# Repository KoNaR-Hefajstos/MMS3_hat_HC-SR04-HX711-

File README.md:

# Hat 4x HC-SR04 i Przetwornika Tensometrycznego HX711

## Sekcja 1: Dokumentacja Hat'a

### Krótki opis projektu
Hat obsługuje cztery zewnętrzne ultradźwiękowe czujniki odległości HC-SR04 oraz dwukanałowey, 24-bitowego przetwornika dla belek tensometrycznych HX711.

Sercem modułu jest mikrokontroler **CH32V003**, który odczytuje dane z czujników i udostępnia je do odczytu po I2C

### Zgodność ze standardem ChainBus

* ✅ Używa złącza ChainBus, nie zmienia jego miejsca ani pinoutu.
* ✅ Używa wyłącznie interfejsu I2C do komunikacji zewnętrznej (działa jako Slave, nie inicjuje transmisji jako Master).
* ✅ Spełnia wymagania mechaniczne standardu (wymiary PCB, rozstaw otworów).
* ✅ Pobiera prąd mieszczący się w limitach wyznaczonych dla pojedynczego modułu (CH32V003 może wyzwalać czujniki ultradźwiękowe sekwencyjnie w celu redukcji zakłóceń i szpilek prądowych).
* ✅ Obsługuje napięcie wejściowe BRD_VIN do wartości 48V.

### Komunikacja i adresowanie

#### Adresacja I2C
Komunikacja z modułem nadrzędnym odbywa się przez magistralę I2C. Adres mikrokontrolera CH32V003 jest definiowany programowo.

| Układ (IC)   | Funkcja                               |     Adres I2C (7-bit)     |
| :----------- | :------------------------------------ | :-----------------------: |
| **CH32V003** | Mikrokontroler (konwerter protokołów) | *Konfigurowalny w sofcie* |
| **M24C64-W** | Pamięć EEPROM (identyfikacja modułu)  |     `1010000b` (0x50)     |

### Pinout mikrokontrolera CH32V003

Rozprowadzenie sygnałów sterujących na piny mikrokontrolera przedstawia poniższa tabela:

| Pin MCU | Nazwa sygnału | Kierunek | Opis funkcjonalny                                              |
| :------ | :------------ | :------: | :------------------------------------------------------------- |
| **PC0** | `ECHO #1`     | Wejście  | Sygnał Echo z czujnika ultradźwiękowego nr 1                   |
| **PC1** | `SDA`         | Wej/Wyj  | Linia danych magistrali I2C (ChainBus)                         |
| **PC2** | `SCL`         | Wejście  | Linia zegarowa magistrali I2C (ChainBus)                       |
| **PC3** | `TRIG #1`     | Wyjście  | Sygnał wyzwalający (Trigger) dla czujnika nr 1                 |
| **PC4** | `ECHO #2`     | Wejście  | Sygnał Echo z czujnika ultradźwiękowego nr 2                   |
| **PC5** | `TRIG #2`     | Wyjście  | Sygnał wyzwalający (Trigger) dla czujnika nr 2                 |
| **PC6** | `ECHO #3`     | Wejście  | Sygnał Echo z czujnika ultradźwiękowego nr 3                   |
| **PC7** | `TRIG #3`     | Wyjście  | Sygnał wyzwalający (Trigger) dla czujnika nr 3                 |
| **PD0** | `ECHO #4`     | Wejście  | Sygnał Echo z czujnika ultradźwiękowego nr 4                   |
| **PD2** | `TRIG #4`     | Wyjście  | Sygnał wyzwalający (Trigger) dla czujnika nr 4                 |
| **PD3** | `RATE_HX`     | Wyjście  | Wybór prędkości próbkowania HX711 (`0` = 10 SPS, `1` = 80 SPS) |
| **PD4** | `PD_SCK_HX`   | Wyjście  | Zegar transmisji oraz wyłączenie zasilania (Power Down) HX711  |
| **PD5** | `DEBUG_TX`    | Wyjście  | Wyjście do debugowania (USART TX)                              |
| **PD6** | `DOUT_HX`     | Wejście  | Wyjście danych szeregowych z przetwornika HX711                |

Dodatkowo na PD6 jest podłączona dioda, można jej użyć do debugowania
---

### Pinout złączy zewnętrznych

#### Złącza czujników ultradźwiękowych
Moduł posiada cztery  złącza w do podłączenia czujników odległości HC-SR04.

| Pin złącza | Nazwa sygnału | Opis                                          |
| :--------: | :------------ | :-------------------------------------------- |
|   **1**    | `5V`          | Zasilanie czujnika (5V z magistrali ChainBus) |
|   **2**    | `TRIG`        | Sygnał wyzwalający                            |
|   **3**    | `ECHO`        | Sygnał powrotny                               |
|   **4**    | `GND`         | Masa zasilania                                |

#### Złącze belki tensometrycznej (J5)
Złącze przeznaczone do podłączenia czujnika siły / wagi (belki tensometrycznej w układzie mostka Wheatstone'a). Sygnały wejściowe są dopasowane do specyfikacji Kanału B układu HX711.

| Pin złącza | Nazwa sygnału | Opis                                              |
| :--------: | :------------ | :------------------------------------------------ |
|   **1**    | `EX+` (E+)    | Dodatnie napięcie zasilania mostka (Excitation +) |
|   **2**    | `INB+`        | Dodatni sygnał wyjściowy z mostka (Input B+)      |
|   **3**    | `INB-`        | Ujemny sygnał wyjściowy z mostka (Input B-)       |
|   **4**    | `GND` (E-)    | Masa zasilania mostka (Excitation -)              |

#### Złącze programowania mikrokontrolera (J7)
Złącze debugowania i programowania struktury CH32V003 przy użyciu WCH Link-E.

| Pin złącza | Nazwa sygnału | Opis                                                      |
| :--------: | :------------ | :-------------------------------------------------------- |
|   **1**    | `SWIO`        | Linia danych SWD (podłączona do pinu PD1 mikrokontrolera) |
|   **2**    | `GND`         | Masa odniesienia                                          |
|   **3**    | `3V3`         | Zasilanie układu logiki (3.3V)                            |

---
### Szczegółowy opis działania układu

#### Sekcja ultradźwiękowa (HC-SR04)
Mikrokontroler CH32V003 cyklicznie generuje impuls wyzwalający piny `TRIG x`. Następnie mierzy czas trwania stanu wysokiego na powiązanym pinie `ECHO x`. Pomiar ten jest przeliczany na odległość zapisywany w rejestrach wewnętrznych MCU, gotowych do odczytu przez magistralę I2C.

#### Sekcja wagowa (HX711)
Układ HX711 przetwarza mikrowoltowe różnice napięć z mostka tensometrycznego na postać cyfrową.
* **Proces odczytu:** MCU monitoruje stan linii `DOUT_HX` (PD6). Gdy linia przejdzie w stan niski, oznacza to gotowość danych. Mikrokontroler taktuje linię `PD_SCK_HX` (PD4), odczytując kolejno 24 bity danych, a następnie generuje dodatkowe impulsy w celu konfiguracji następnego pomiaru (np. 26 impulsów, aby utrzymać odczyt z Kanału B ze wzmocnieniem 32).

#### Charakterystyka i parametry przetwornika HX711

Układ HX711 jest dedykowanym, 24-bitowym przetwornikiem ADC ze zintegrowanym niskoszumnym przedwzmacniaczem (PGA). Posiada on dwa różnicowe kanały wejściowe, które różnią się zakresem napięć oraz czułością:

#### Różnice między Kanałem A i Kanałem B

1. **Wzmocnienie i zakresy wejściowe (przy zasilaniu $V_{DD} = 5\text{V}$):**
   * **Kanał A:** Posiada programowalny stopień wzmocnienia równy **128** lub **64**.
     * Dla wzmocnienia **128**: zakres napięcia wejściowego wynosi **$\pm 20\text{ mV}$** (pełna skala). Jest to najbardziej czuły zakres, zalecany dla większości typowych belek tensometrycznych.
     * Dla wzmocnienia **64**: zakres napięcia wejściowego wynosi **$\pm 40\text{ mV}$**.
   * **Kanał B:** Posiada stałe, fabrycznie zdefiniowane wzmocnienie **32**.
     * Zakres napięcia wejściowego wynosi **$\pm 80\text{ mV}$**. Kanał ten, dzięki szerszemu zakresowi i mniejszej czułości, doskonale nadaje się do obsługi czujników o wyższym poziomie sygnału wyjściowego lub pomiarów pomocniczych.

2. **Wybór aktywnego kanału:**
   Multipleksacja kanałów wejściowych odbywa się programowo poprzez podanie odpowiedniej liczby impulsów zegarowych na pin `PD_SCK` po odczytaniu danych (wejście `DOUT` w stanie niskim):
   * **25 impulsów zegarowych:** następny pomiar na Kanale A ze wzmocnieniem 128,
   * **26 impulsów zegarowych:** następny pomiar na Kanale B ze wzmocnieniem 32,
   * **27 impulsów zegarowych:** następny pomiar na Kanale A ze wzmocnieniem 64.

3. **Częstotliwość próbkowania (SPS):**
   Prędkość konwersji jest ustawiana sprzętowo poprzez stan pinu `RATE_HX` (PD3):
   * Stan niski (`0`): **10 SPS** (próbek na sekundę). Zapewnia najniższy poziom szumów i najwyższą stabilność pomiarów wagowych (zalecane).
   * Stan wysoki (`1`): **80 SPS**. Zwiększa dynamikę pomiarów kosztem nieznacznego wzrostu szumu przetwornika.

---

---

### Gotowe arkusze hierarchiczne
W projekcie zaprojektowano i użyto następujących arkuszy hierarchicznych:
* **CH32v003** – Arkusz mikrokontrolera
* **Ultrasonic_HC-SR04** – Arkusz z podłączeniem HC-SR04 oraz dzielnikami napięcie 5V -> 3V3.
* **HX711_LoadCell** – Układ przetwornika HX711 ze wszytkimi elementami pasywnymi i złaczem

---

## Sekcja 2: Specyfikacja standardu ChainBus

### Architektura i łączenie modułów
Standard ChainBus umożliwia modułowe łączenie hatów. Na jednym MMS3 można zamontować pionowo **do 8 hat'ów**. Połączenie realizowane jest poprzez wpięcie złącza męskiego kolejnego hat'a w złącze żeńskie poprzedniego.

### Komunikacja i sterowanie
Magistrala ChainBus jest w pełni cyfrowa. Płyta główna nie steruje bezpośrednio sygnałami ogólnego przeznaczenia (GPIO) na poszczególnych hat'ach. Wszelkie operacje (np. odczyt czujników, sterowanie) muszą być realizowane przez dedykowane układy scalone komunikujące się przez interfejsy systemowe.

Wybór aktywnego modułu realizowany jest przez układ przełącznika magistrali (bus switch) na płycie głównej. Dzięki temu linie I2C, SPI i UART są niezależne dla każdego hat'a (brak konfliktów adresów I2C między różnymi hatami).
* **Identyfikacja:** Każdy moduł powinien posiadać pamięć EEPROM na magistrali I2C w celu identyfikacji płyty przez system - układ M24C64-W skonfigurowany na adres `1010000` przy liniach adresowych A0, A1, A2 zwartych do masy.

### Zasilanie
Złącze ChainBus dostarcza następujące linie zasilania:

| Magistrala zasilania | Napięcie znamionowe | Maksymalny prąd (łączny dla 8 hatów) | Szacowany prąd na jeden hat |
| :------------------- | :-----------------: | :----------------------------------: | :-------------------------: |
| **5V**               |        5.0 V        |                1.0 A                 |           125 mA            |
| **12V stby**         |       12.0 V        |                0.5 A                 |            65 mA            |
| **BRD_VIN**          |   12.0 V – 48.0 V   |                1.5 A                 |           185 mA            |

*   Komponenty podłączone do linii `BRD_VIN` muszą być przystosowane do pracy z napięciem od 12V do **48 V**.

---

## Sekcja 3: Licencje

### Licencje projektu

*   **PCB:** CERN-OHL-P
*   **Software:** MIT License

[Template](https://github.com/KoNaR-Hefajstos/MMS3_hat_templates/) jest na licencji CC0 1.0 Universal. **Reszta projektu nie jest na tej licencji**

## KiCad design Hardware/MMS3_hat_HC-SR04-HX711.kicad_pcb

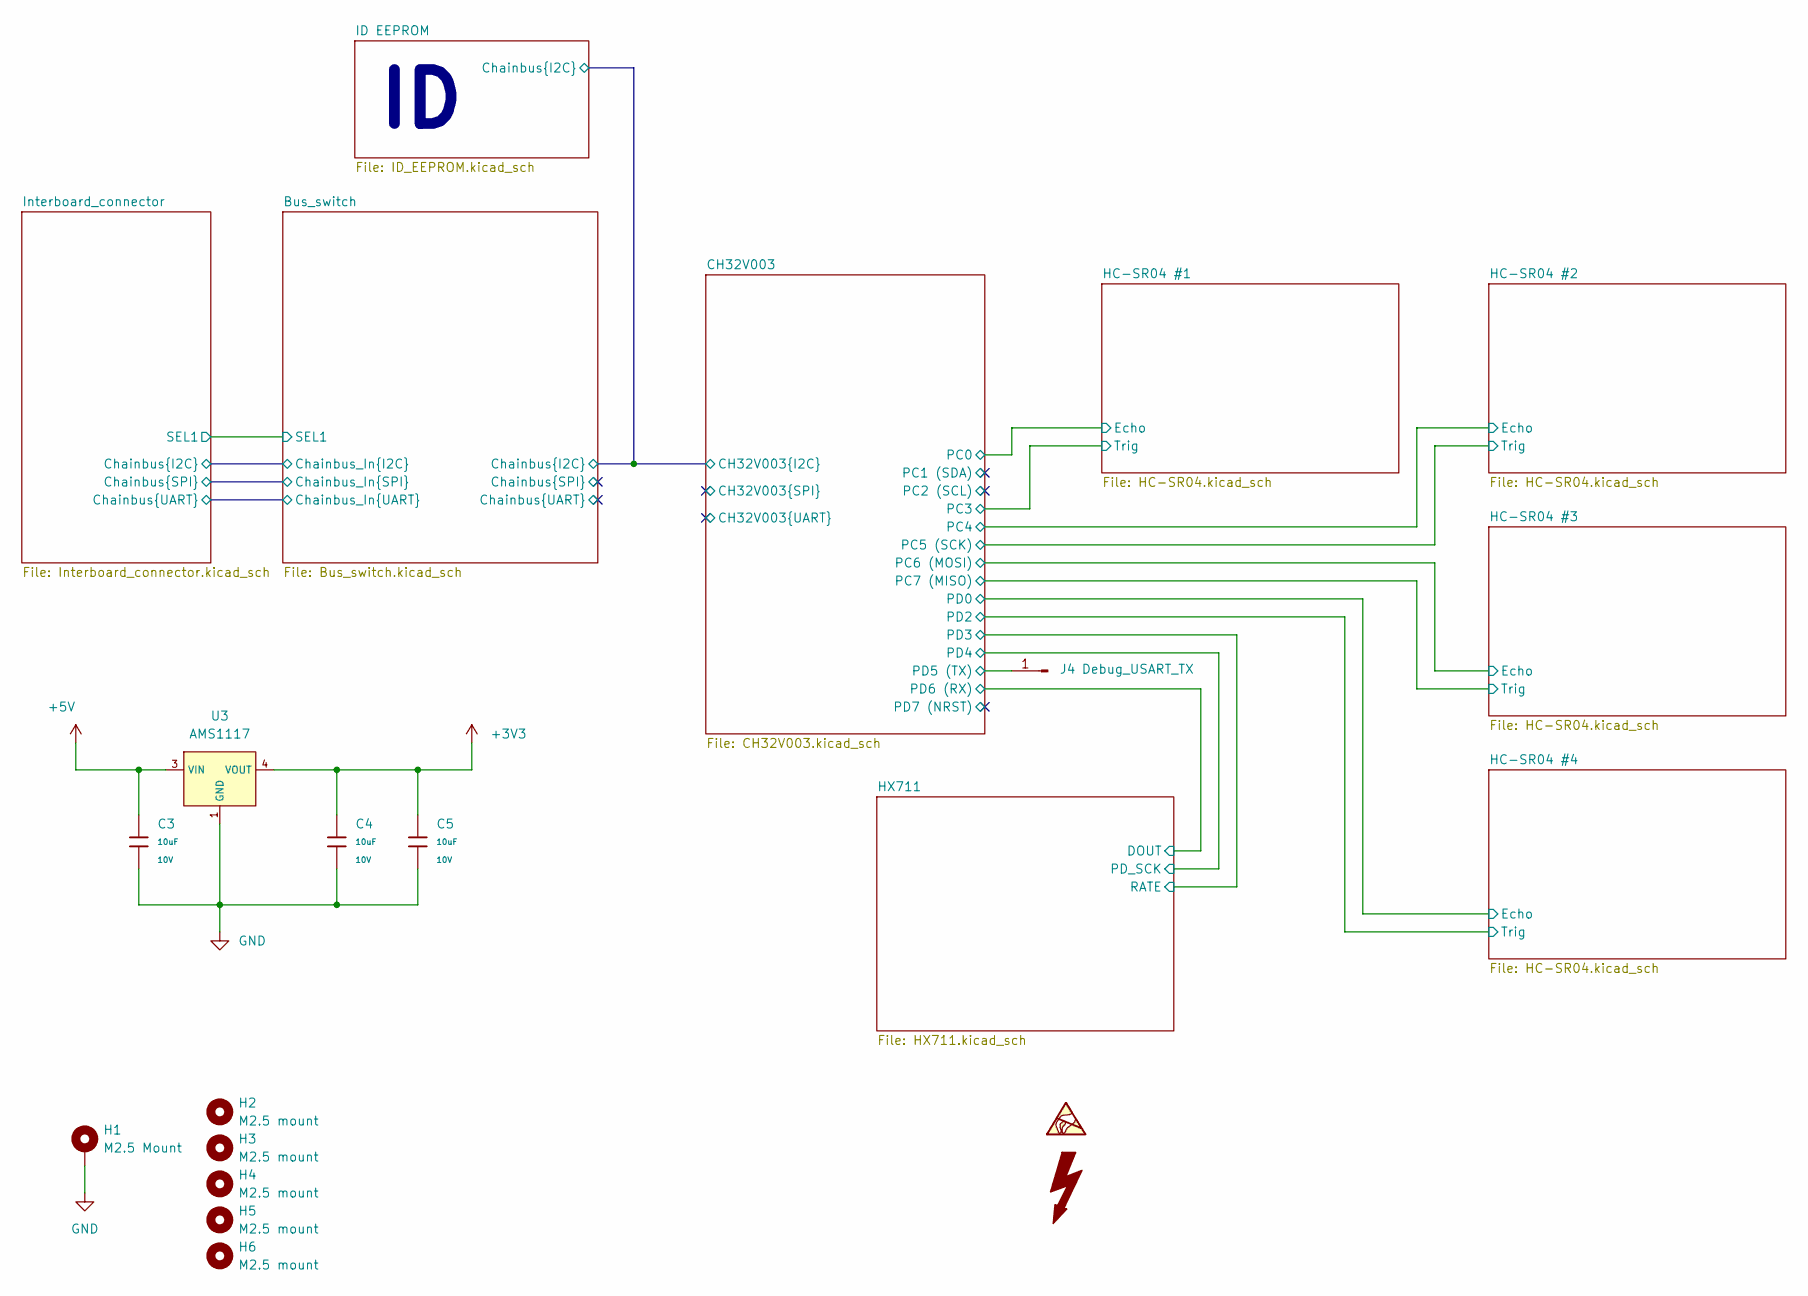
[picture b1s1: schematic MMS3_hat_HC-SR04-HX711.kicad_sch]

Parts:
C3, C4, C5: 10uF; C_0603; Voltage Rated 10V; Tolerance ±10%; Part CL10A106KP8NNNC; LCSC C19702
H1: M2.5 Mount; MountingHole_2.7mm_M2.5_DIN965_Pad_TopOnly
H2, H3, H4, H5, H6: M2.5 mount; MountingHole_2.7mm_M2.5
J4: Debug_USART_TX; PinSocket_1x01_P2.54mm_Vertical
U3: AMS1117; SOT-223-3_L6.5-W3.4-P2.30-LS7.0-BR; Output Voltage 3.3V; Dropout Voltage 1.3V@(800mA); Part AMS1117-3.3; LCSC C6186

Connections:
+3V3: C4.1, C5.1, U3.2 (VOUT), U3.4 (VOUT); also elsewhere on the board
+5V: C3.1, U3.3 (VIN); also elsewhere on the board
/CH32V003/CH32V003.TX: J4.1 (Pin_1_1); also elsewhere on the board
GND: C3.2, C4.2, C5.2, H1.1 (1_1), U3.1 (GND); also elsewhere on the board

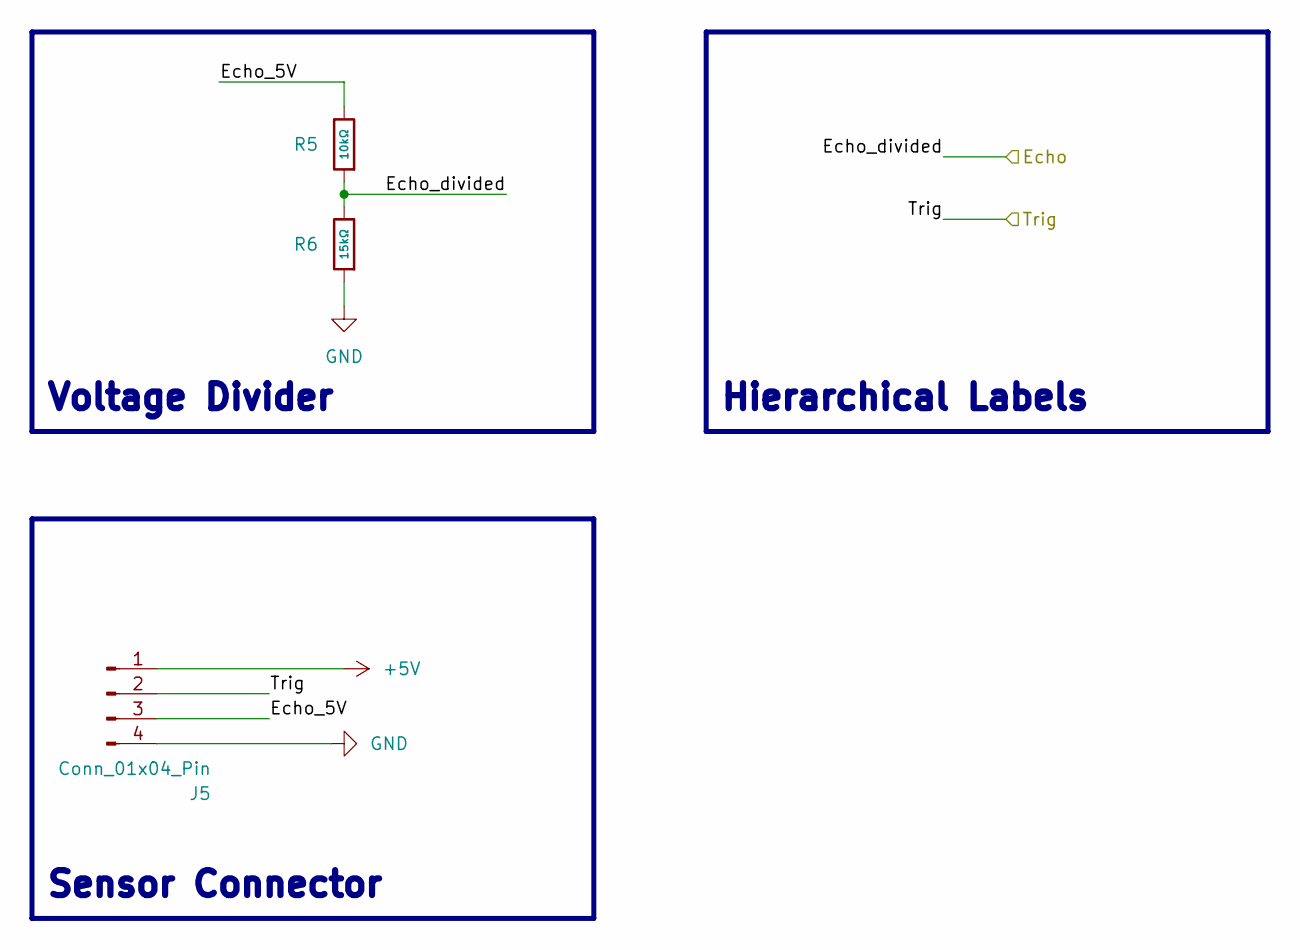
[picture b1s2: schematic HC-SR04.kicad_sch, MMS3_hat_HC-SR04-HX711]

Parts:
J5: Conn_01x04_Pin; JST_XH_S4B-XH-A_1x04_P2.50mm_Horizontal
R5: 10kΩ; R_0402; Overload Voltage (Max) 50V; Tolerance ±1%; Part 0402WGF1002TCE; LCSC C25744
R6: 15kΩ; R_0402; Overload Voltage (Max) 50V; Tolerance ±1%; Part 0402WGF1502TCE; LCSC C25756

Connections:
+5V: J5.1; also elsewhere on the board
/CH32V003/PC0: R5.1, R6.2; also elsewhere on the board
/CH32V003/PC3: J5.2; also elsewhere on the board
/HC-SR04 #1/Echo_5V: J5.3, R5.2
GND: J5.4, R6.1; also elsewhere on the board

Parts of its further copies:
J6, J10, J11: Conn_01x04_Pin; JST_XH_S4B-XH-A_1x04_P2.50mm_Horizontal
R7, R19, R21: 10kΩ; R_0402; Overload Voltage (Max) 50V; Tolerance ±1%; Part 0402WGF1002TCE; LCSC C25744
R8, R20, R22: 15kΩ; R_0402; Overload Voltage (Max) 50V; Tolerance ±1%; Part 0402WGF1502TCE; LCSC C25756

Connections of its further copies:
+5V: J6.1, J10.1, J11.1; also elsewhere on the board
/CH32V003/CH32V003.MISO: J11.2; also elsewhere on the board
/CH32V003/CH32V003.MOSI: R21.1, R22.2; also elsewhere on the board
/CH32V003/CH32V003.SCK: J6.2; also elsewhere on the board
/CH32V003/PC4: R7.1, R8.2; also elsewhere on the board
/CH32V003/PD0: R19.1, R20.2; also elsewhere on the board
/CH32V003/PD2: J10.2; also elsewhere on the board
/HC-SR04 #2/Echo_5V: J6.3, R7.2
/HC-SR04 #3/Echo_5V: J11.3, R21.2
/HC-SR04 #4/Echo_5V: J10.3, R19.2
GND: J6.4, J10.4, J11.4, R8.1, R20.1, R22.1; also elsewhere on the board

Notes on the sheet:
Voltage Divider
Sensor Connector
Hierarchical Labels

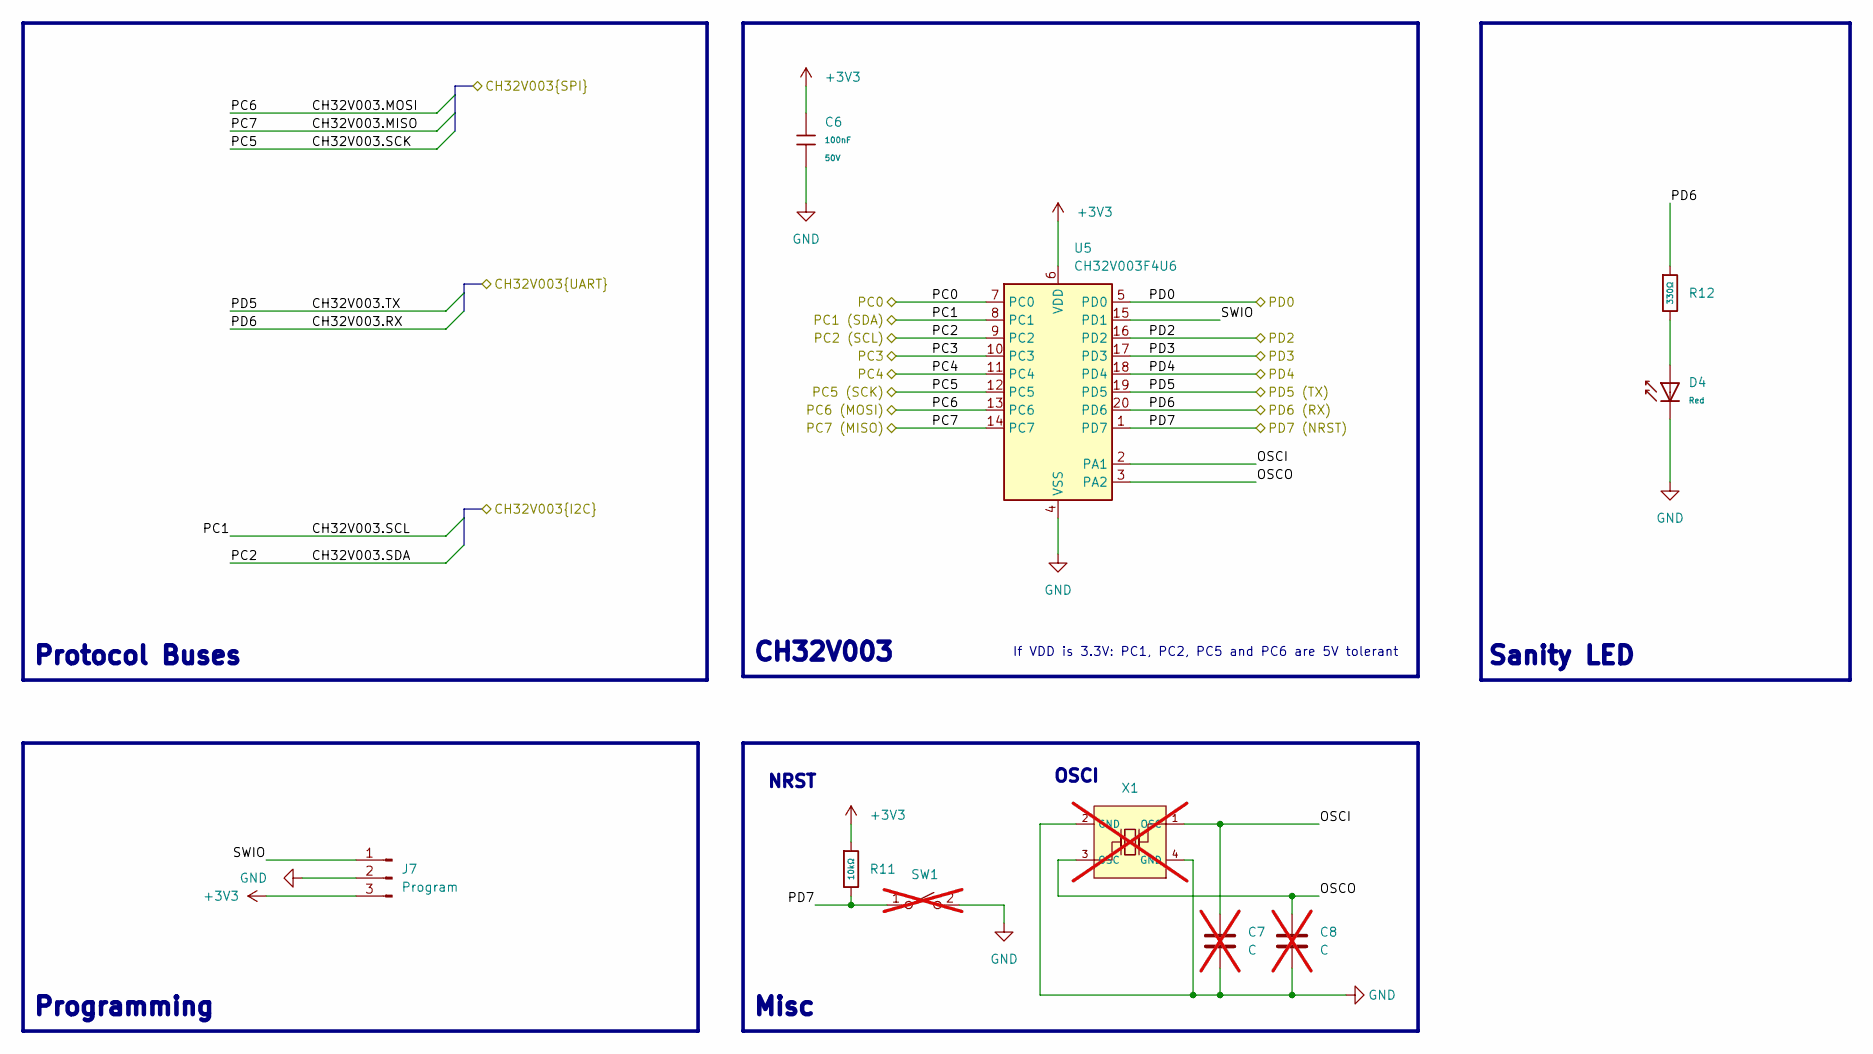
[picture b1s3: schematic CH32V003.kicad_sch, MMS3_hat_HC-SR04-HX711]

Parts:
C6: 100nF; C_0603; Voltage Rated 50V; Tolerance ±10%; Part CC0603KRX7R9BB104; LCSC C14663
C7, C8: C; not fitted
D4: Red; D_0603; Part KT-0603R; LCSC C2286
J7: Program; JST_XH_B3B-XH-A_1x03_P2.50mm_Vertical
R11: 10kΩ; R_0402; Overload Voltage (Max) 50V; Tolerance ±1%; Part 0402WGF1002TCE; LCSC C25744
R12: 330Ω; R_0402; Overload Voltage (Max) 50V; Tolerance ±1%; Part 0402WGF3300TCE; LCSC C25104
SW1: SW_SPST; not fitted
U5: CH32V003F4U6; QFN-20-1EP_3x3mm_P0.4mm_EP1.65x1.65mm; LCSC C5299908
X1: X322525MOB4SI; OSC-SMD_4P-L3.2-W2.5-BL; Frequency Tolerance ±10ppm; Part X322525MOB4SI; LCSC C9006; not fitted

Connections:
+3V3: C6.1, J7.3, R11.1, U5.6 (VDD); also elsewhere on the board
/Bus_switch/Chainbus.SCL: U5.8 (PC1); also elsewhere on the board
/Bus_switch/Chainbus.SDA: U5.9 (PC2); also elsewhere on the board
/CH32V003/CH32V003.MISO: U5.14 (PC7); also elsewhere on the board
/CH32V003/CH32V003.MOSI: U5.13 (PC6); also elsewhere on the board
/CH32V003/CH32V003.RX: R12.1, U5.20 (PD6); also elsewhere on the board
/CH32V003/CH32V003.SCK: U5.12 (PC5); also elsewhere on the board
/CH32V003/CH32V003.TX: U5.19 (PD5); also elsewhere on the board
/CH32V003/OSCI: C7.1, U5.2 (PA1), X1.1 (OSC)
/CH32V003/OSCO: C8.1, U5.3 (PA2), X1.3 (OSC)
/CH32V003/PC0: U5.7 (PC0); also elsewhere on the board
/CH32V003/PC3: U5.10 (PC3); also elsewhere on the board
/CH32V003/PC4: U5.11 (PC4); also elsewhere on the board
/CH32V003/PD0: U5.5 (PD0); also elsewhere on the board
/CH32V003/PD2: U5.16 (PD2); also elsewhere on the board
/CH32V003/PD3: U5.17 (PD3); also elsewhere on the board
/CH32V003/PD4: U5.18 (PD4); also elsewhere on the board
/CH32V003/PD7: R11.2, SW1.1 (A), U5.1 (PD7)
/CH32V003/SWIO: J7.1, U5.15 (PD1)
GND: C6.2, C7.2, C8.2, D4.1, J7.2, SW1.2 (B), U5.4 (VSS), U5.21 (VSS), X1.2 (GND), X1.4 (GND); also elsewhere on the board
unnamed: D4.2, R12.2

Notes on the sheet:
NRST
Sanity LED
If VDD is 3.3V: PC1, PC2, PC5 and PC6 are 5V tolerant
CH32V003
OSCI
Protocol Buses
Misc
Programming

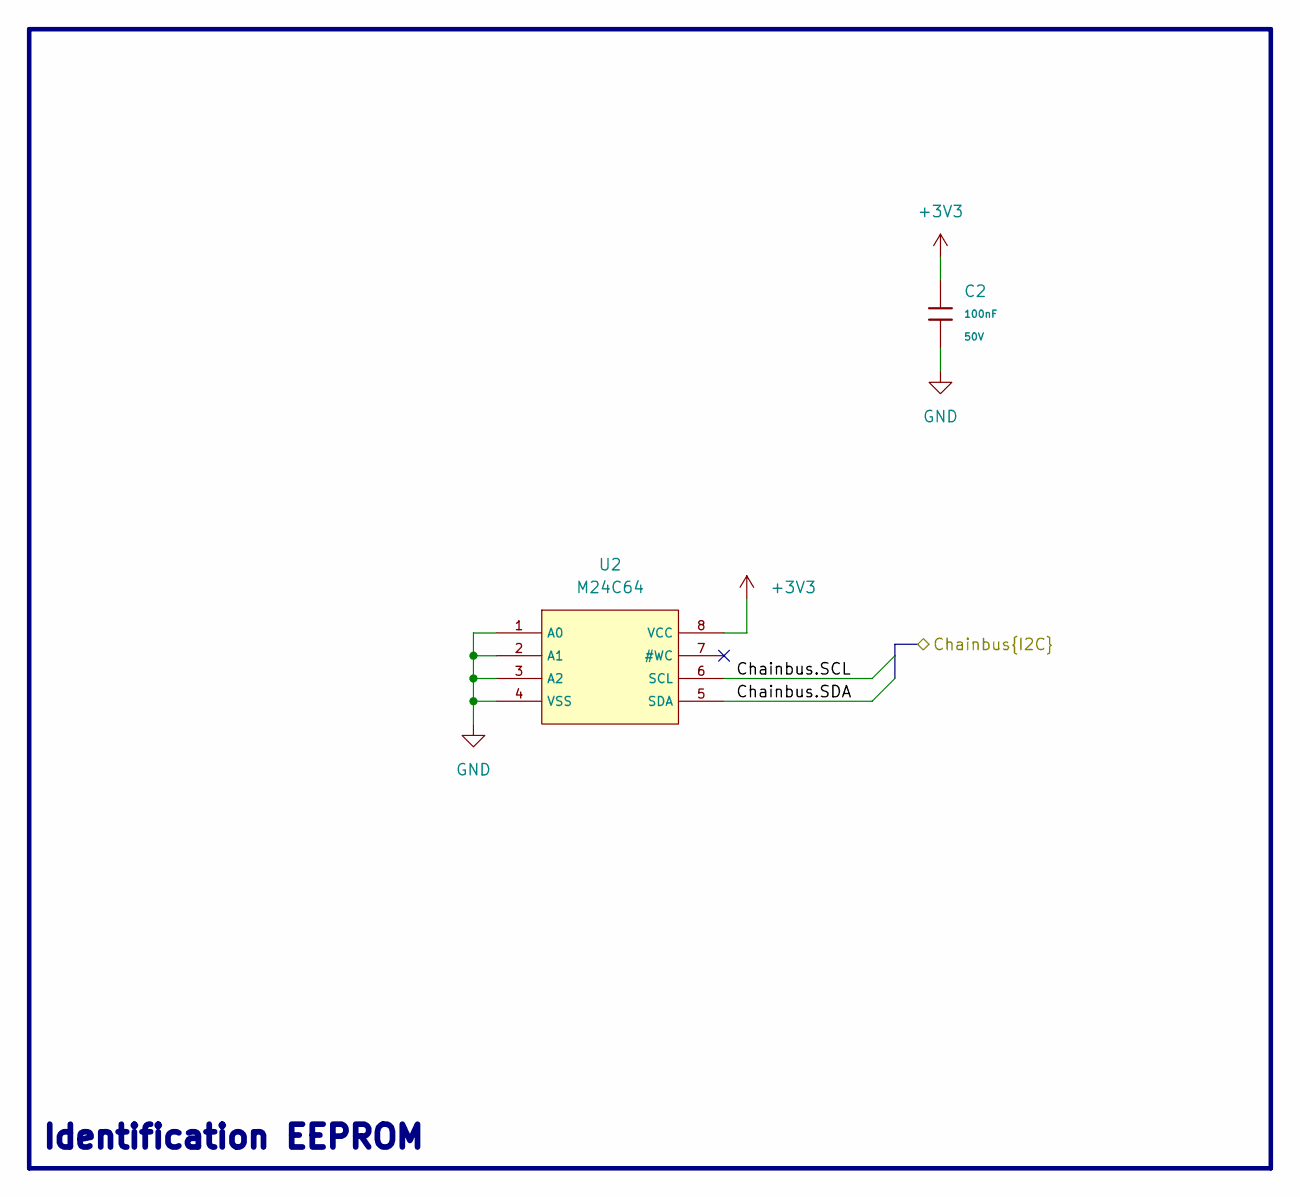
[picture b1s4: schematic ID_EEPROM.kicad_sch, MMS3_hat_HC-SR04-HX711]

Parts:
C2: 100nF; C_0603; Voltage Rated 50V; Tolerance ±10%; Part CC0603KRX7R9BB104; LCSC C14663
U2: M24C64; SOIC-8_L5.0-W4.0-P1.27-LS6.0-BL; Supply Voltage 1.8V~5.5V; Part M24C64-RMN6TP; LCSC C79988

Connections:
+3V3: C2.1, U2.8 (VCC); also elsewhere on the board
/Bus_switch/Chainbus.SCL: U2.6 (SCL); also elsewhere on the board
/Bus_switch/Chainbus.SDA: U2.5 (SDA); also elsewhere on the board
GND: C2.2, U2.1 (A0), U2.2 (A1), U2.3 (A2), U2.4 (VSS); also elsewhere on the board

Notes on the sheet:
Identification EEPROM

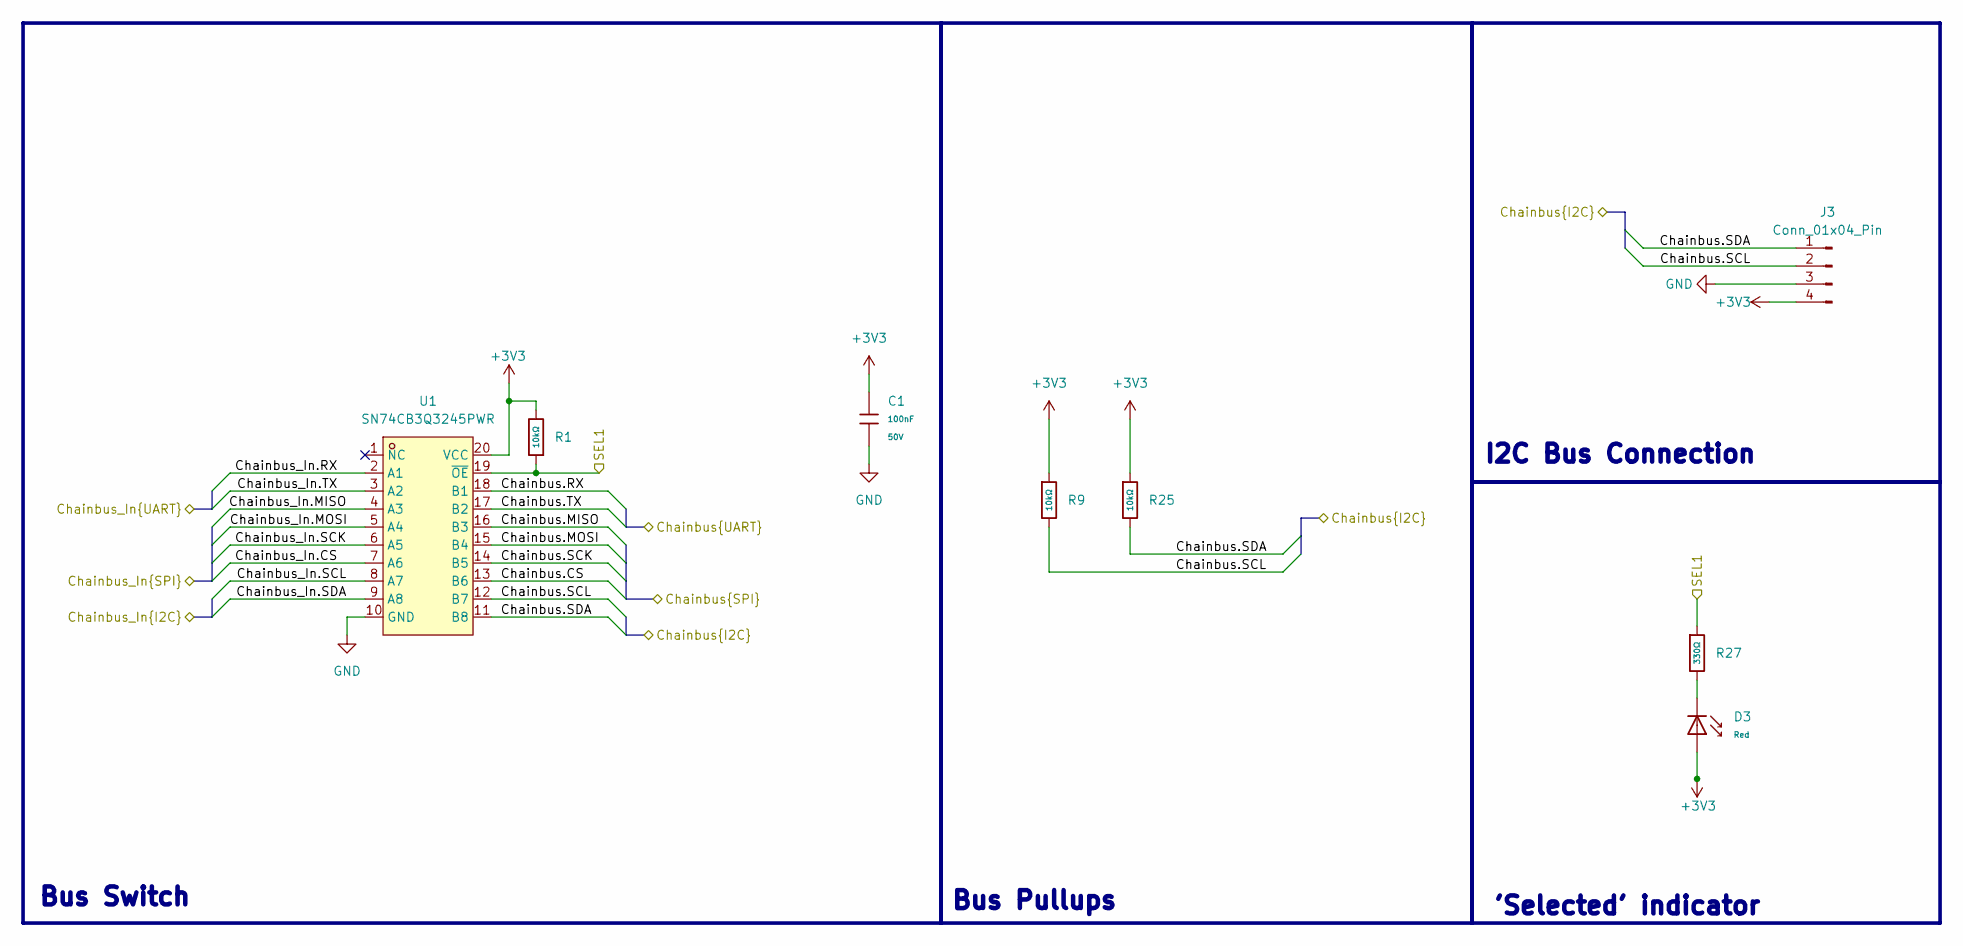
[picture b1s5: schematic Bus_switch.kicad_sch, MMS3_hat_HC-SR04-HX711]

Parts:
C1: 100nF; C_0603; Voltage Rated 50V; Tolerance ±10%; Part CC0603KRX7R9BB104; LCSC C14663
D3: Red; D_0603; Part KT-0603R; LCSC C2286
J3: Conn_01x04_Pin; PinHeader_1x04_P2.54mm_Vertical
R1, R9, R25: 10kΩ; R_0402; Overload Voltage (Max) 50V; Tolerance ±1%; Part 0402WGF1002TCE; LCSC C25744
R27: 330Ω; R_0402; Overload Voltage (Max) 50V; Tolerance ±1%; Part 0402WGF3300TCE; LCSC C25104
U1: SN74CB3Q3245PWR; TSSOP-20_L6.5-W4.4-P0.65-LS6.4-BL; MPN SN74CB3Q3245PWR; LCSC Part C470961

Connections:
+3V3: C1.1, D3.2, J3.4, R1.2, R9.1, R25.1, U1.20 (VCC); also elsewhere on the board
/Bus_switch/Chainbus.CS: U1.13 (B6)
/Bus_switch/Chainbus.MISO: U1.16 (B3)
/Bus_switch/Chainbus.MOSI: U1.15 (B4)
/Bus_switch/Chainbus.RX: U1.18 (B1)
/Bus_switch/Chainbus.SCK: U1.14 (B5)
/Bus_switch/Chainbus.SCL: J3.2, R9.2, U1.12 (B7); also elsewhere on the board
/Bus_switch/Chainbus.SDA: J3.1, R25.2, U1.11 (B8); also elsewhere on the board
/Bus_switch/Chainbus.TX: U1.17 (B2)
/Bus_switch/Chainbus_In.CS: U1.7 (A6); also elsewhere on the board
/Bus_switch/Chainbus_In.MISO: U1.4 (A3); also elsewhere on the board
/Bus_switch/Chainbus_In.MOSI: U1.5 (A4); also elsewhere on the board
/Bus_switch/Chainbus_In.RX: U1.2 (A1); also elsewhere on the board
/Bus_switch/Chainbus_In.SCK: U1.6 (A5); also elsewhere on the board
/Bus_switch/Chainbus_In.SCL: U1.8 (A7); also elsewhere on the board
/Bus_switch/Chainbus_In.SDA: U1.9 (A8); also elsewhere on the board
/Bus_switch/Chainbus_In.TX: U1.3 (A2); also elsewhere on the board
/Bus_switch/SEL1: R1.1, R27.1, U1.19 (~OE); also elsewhere on the board
GND: C1.2, J3.3, U1.10 (GND); also elsewhere on the board
unnamed: D3.1, R27.2

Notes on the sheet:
Bus Switch
Bus Pullups
'Selected' indicator
I2C Bus Connection

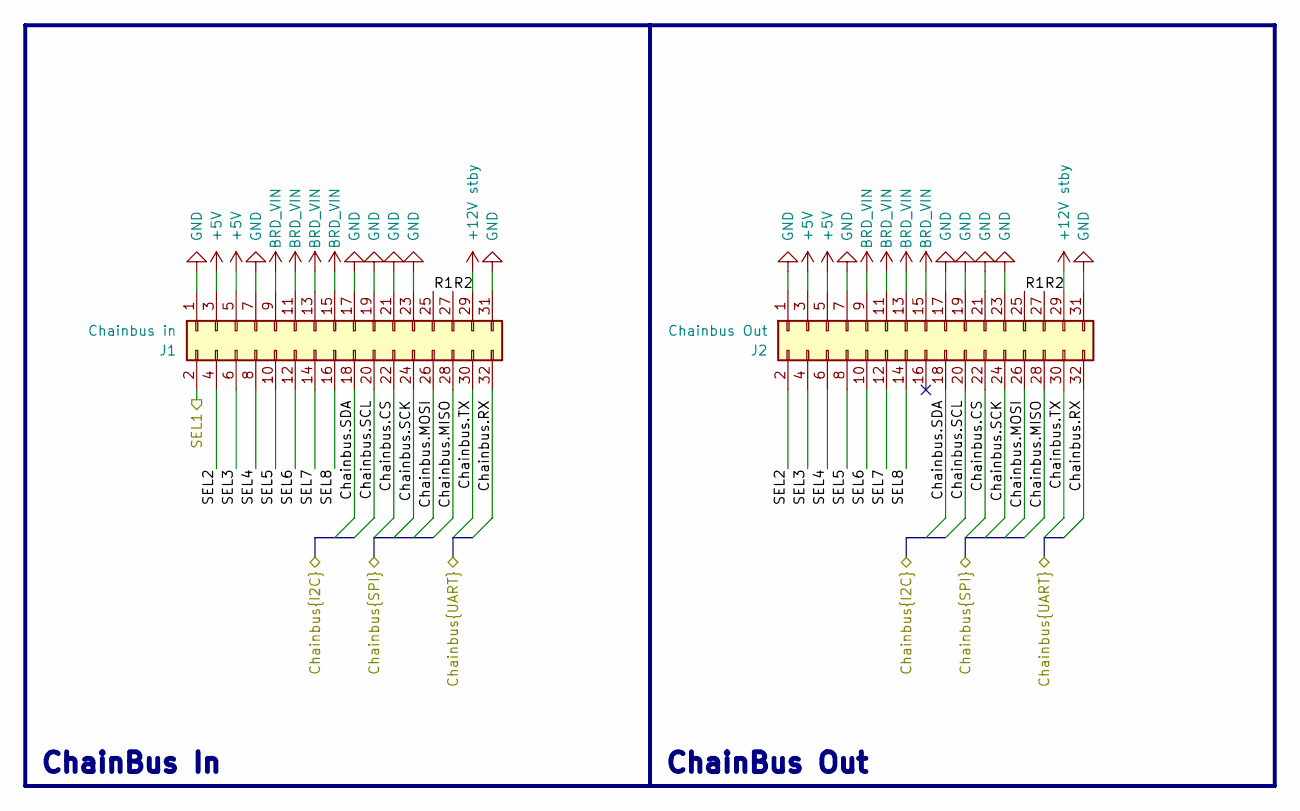
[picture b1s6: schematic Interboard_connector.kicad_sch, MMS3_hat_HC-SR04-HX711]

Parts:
J1: Chainbus in; PinHeader_2x16_P2.54mm_Vertical_SMD
J2: Chainbus Out; PinSocket_2x16_P2.54mm_Vertical_SMD

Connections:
+5V: J1.3, J1.5, J2.3, J2.5; also elsewhere on the board
+12V stby: J1.29, J2.29
/Bus_switch/Chainbus_In.CS: J1.22, J2.22; also elsewhere on the board
/Bus_switch/Chainbus_In.MISO: J1.28, J2.28; also elsewhere on the board
/Bus_switch/Chainbus_In.MOSI: J1.26, J2.26; also elsewhere on the board
/Bus_switch/Chainbus_In.RX: J1.32, J2.32; also elsewhere on the board
/Bus_switch/Chainbus_In.SCK: J1.24, J2.24; also elsewhere on the board
/Bus_switch/Chainbus_In.SCL: J1.20, J2.20; also elsewhere on the board
/Bus_switch/Chainbus_In.SDA: J1.18, J2.18; also elsewhere on the board
/Bus_switch/Chainbus_In.TX: J1.30, J2.30; also elsewhere on the board
/Bus_switch/SEL1: J1.2; also elsewhere on the board
/Interboard_connector/R1: J1.25, J2.25
/Interboard_connector/R2: J1.27, J2.27
/Interboard_connector/SEL2: J1.4, J2.2
/Interboard_connector/SEL3: J1.6, J2.4
/Interboard_connector/SEL4: J1.8, J2.6
/Interboard_connector/SEL5: J1.10, J2.8
/Interboard_connector/SEL6: J1.12, J2.10
/Interboard_connector/SEL7: J1.14, J2.12
/Interboard_connector/SEL8: J1.16, J2.14
BRD_VIN: J1.9, J1.11, J1.13, J1.15, J2.9, J2.11, J2.13, J2.15
GND: J1.1, J1.7, J1.17, J1.19, J1.21, J1.23, J1.31, J2.1, J2.7, J2.17, J2.19, J2.21, J2.23, J2.31; also elsewhere on the board

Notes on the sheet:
ChainBus In
ChainBus Out

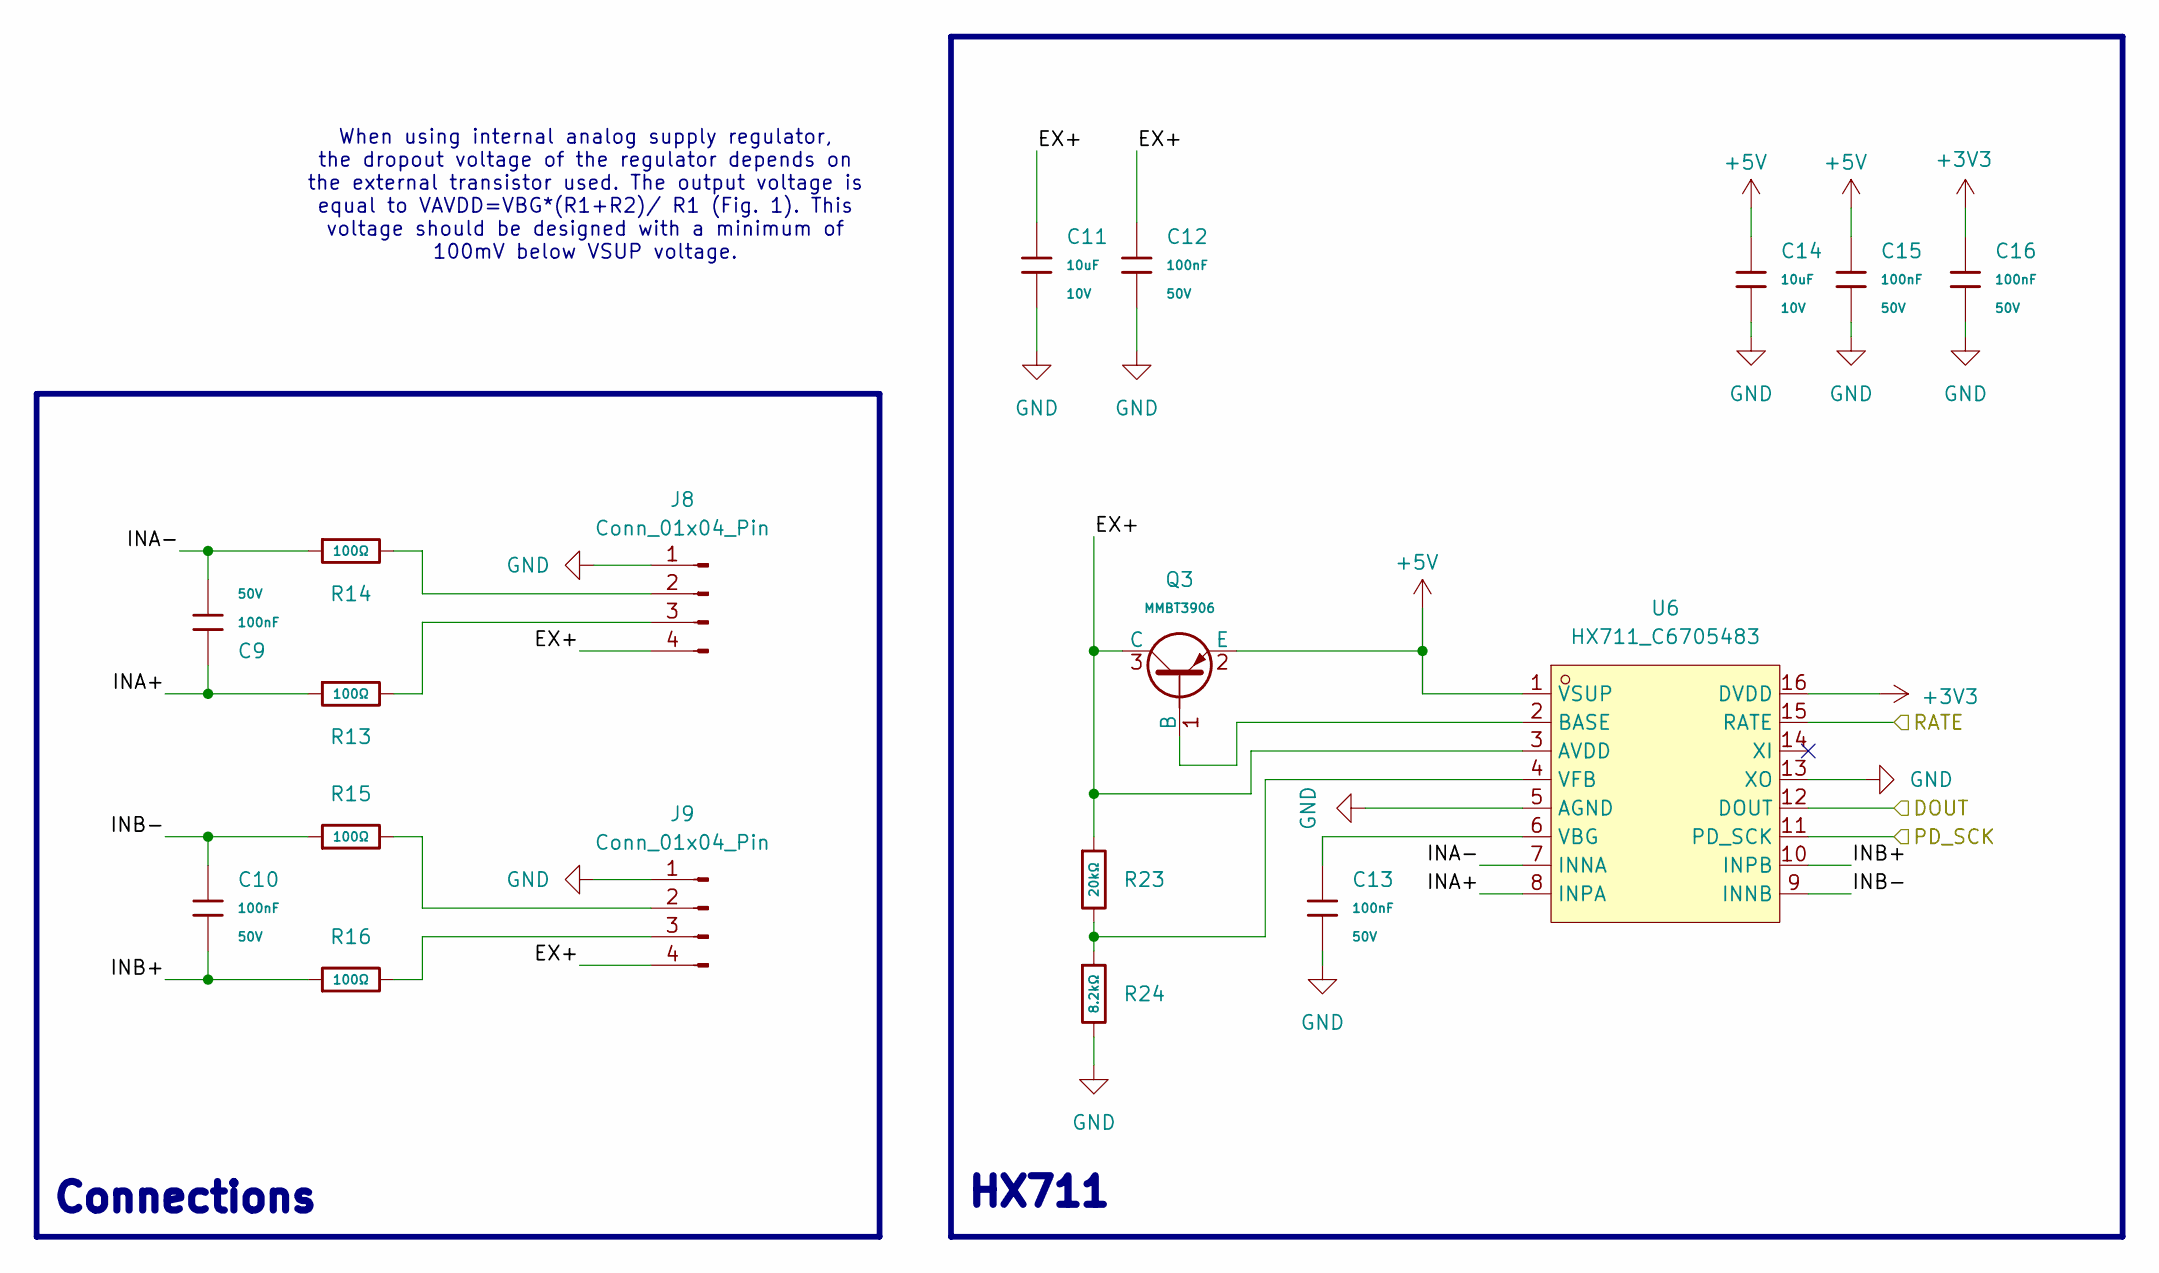
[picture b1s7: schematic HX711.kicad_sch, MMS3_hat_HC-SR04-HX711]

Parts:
C9, C10, C12, C13, C15, C16: 100nF; C_0603; Voltage Rated 50V; Tolerance ±10%; Part CC0603KRX7R9BB104; LCSC C14663
C11, C14: 10uF; C_0603; Voltage Rated 10V; Tolerance ±10%; Part CL10A106KP8NNNC; LCSC C19702
J8, J9: Conn_01x04_Pin; JST_XH_S4B-XH-A_1x04_P2.50mm_Horizontal
Q3: MMBT3906; Q_SOT-23; Part MMBT3906; LCSC C7420354
R13, R14, R15, R16: 100Ω; R_0402; Overload Voltage (Max) 50V; Tolerance ±1%; Part 0402WGF1000TCE; LCSC C25076
R23: 20kΩ; R_0402; Overload Voltage (Max) 50V; Tolerance ±1%; Part 0402WGF2002TCE; LCSC C25765
R24: 8.2kΩ; R_0402; Overload Voltage (Max) 50V; Tolerance ±1%; Part 0402WGF8201TCE; LCSC C25924
U6: HX711_C6705483; SOP-16_L10.0-W3.9-P1.27-LS6.0-BL; MPN HX711; LCSC Part C6705483

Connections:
+3V3: C16.1, U6.16 (DVDD); also elsewhere on the board
+5V: C14.1, C15.1, Q3.2 (E), U6.1 (VSUP); also elsewhere on the board
/CH32V003/CH32V003.RX: U6.12 (DOUT); also elsewhere on the board
/CH32V003/PD3: U6.15 (RATE); also elsewhere on the board
/CH32V003/PD4: U6.11 (PD_SCK); also elsewhere on the board
/HX711/EX+: C11.1, C12.1, J8.4, J9.4, Q3.3 (C), R23.1, U6.3 (AVDD)
/HX711/INA+: C9.1, R13.1, U6.8 (INPA)
/HX711/INA-: C9.2, R14.1, U6.7 (INNA)
/HX711/INB+: C10.2, R16.1, U6.10 (INPB)
/HX711/INB-: C10.1, R15.1, U6.9 (INNB)
GND: C11.2, C12.2, C13.2, C14.2, C15.2, C16.2, J8.1, J9.1, R24.2, U6.5 (AGND), U6.13 (XO); also elsewhere on the board
unnamed: J8.2, R14.2
unnamed: J8.3, R13.2
unnamed: J9.2, R15.2
unnamed: J9.3, R16.2
unnamed: Q3.1 (B), U6.2 (BASE)
unnamed: C13.1, U6.6 (VBG)
unnamed: R23.2, R24.1, U6.4 (VFB)

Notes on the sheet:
Connections
When using internal analog supply regulator, the dropout voltage of the regulator depends on the external transistor used. The output voltage is equal to VAVDD=VBG*(R1+R2)/ R1 (Fig. 1). This voltage should be designed with a minimum of 100mV below VSUP voltage.
HX711
